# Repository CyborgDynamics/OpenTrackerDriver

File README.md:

# OpenTrackerDriver
Arduino Based Star Tracker Motor

This is not ready for use. The code is complete and tested via breadboard. The Kicad is incomplete and wrong.

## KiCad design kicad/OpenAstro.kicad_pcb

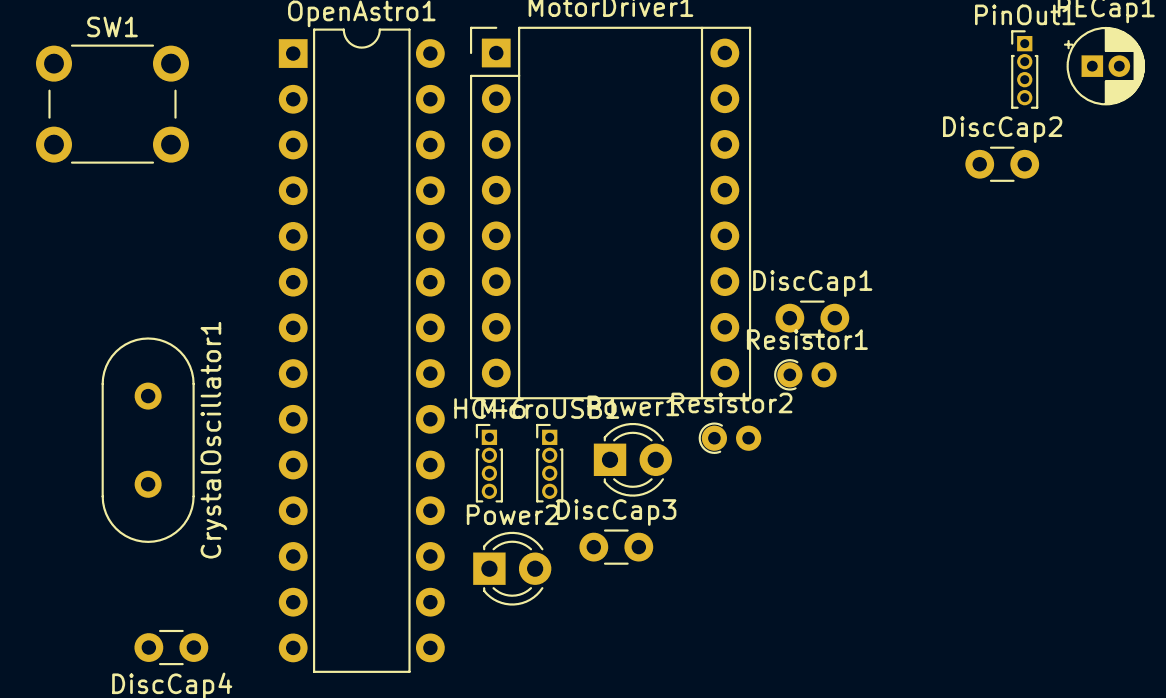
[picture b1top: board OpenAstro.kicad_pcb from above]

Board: 2 copper layers, 16 parts (0 on the bottom side), 17 nets, no tracks yet.

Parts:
CrystalOscillator1: 16.000; Crystal_HC18-U_Vertical
DiscCap1, DiscCap2: 104; C_Disc_D3.0mm_W1.6mm_P2.50mm
DiscCap3, DiscCap4: 220; C_Disc_D3.0mm_W1.6mm_P2.50mm
HC-6: Bluetooth; PinHeader_1x04_P1.00mm_Vertical
MicroUSB1: USB; PinHeader_1x04_P1.00mm_Vertical
MotorDriver1: Pololu_Breakout_A4988; Pololu_Breakout-16_15.2x20.3mm
OpenAstro1: ATmega328P-PU; DIP-28_W7.62mm
PECap1: 100uF; CP_Radial_D4.0mm_P1.50mm
PinOut1: Header; PinHeader_1x04_P1.00mm_Vertical
Power1, Power2: LED; LED_D3.0mm
Resistor1: 430; R_Axial_DIN0204_L3.6mm_D1.6mm_P1.90mm_Vertical
Resistor2: 220; R_Axial_DIN0204_L3.6mm_D1.6mm_P1.90mm_Vertical
SW1: SW_Push; SW_PUSH_6mm_H4.3mm

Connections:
+5V: DiscCap1.1, DiscCap2.1, HC-6.1, MicroUSB1.4, MotorDriver1.2, MotorDriver1.10, MotorDriver1.11, MotorDriver1.12, OpenAstro1.7, OpenAstro1.20, Power1.2
GND: DiscCap1.2, DiscCap2.2, DiscCap3.2, DiscCap4.1, HC-6.2, MicroUSB1.1, MotorDriver1.1, MotorDriver1.7, OpenAstro1.8, OpenAstro1.22, PECap1.2, Resistor1.2, Resistor2.2, SW1.2
unnamed: CrystalOscillator1.1, DiscCap3.1, OpenAstro1.9
unnamed: CrystalOscillator1.2, DiscCap4.2, OpenAstro1.10
unnamed: HC-6.3, OpenAstro1.15
unnamed: HC-6.4, OpenAstro1.16
unnamed: MotorDriver1.3, PinOut1.1
unnamed: MotorDriver1.4, PinOut1.2
unnamed: MotorDriver1.5, PinOut1.3
unnamed: MotorDriver1.6, PinOut1.4
unnamed: MotorDriver1.9, OpenAstro1.14
unnamed: MotorDriver1.15, OpenAstro1.4
unnamed: MotorDriver1.16, OpenAstro1.11
unnamed: OpenAstro1.1, SW1.1
unnamed: Power1.1, Resistor2.1
unnamed: Power2.1, Resistor1.1
VCC: MotorDriver1.8, PECap1.1, Power2.2

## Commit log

2019-09-01 -Initial commit
2019-09-01 -Added Code Files
2019-09-01 -Move and Rename -Add KiCad Files
